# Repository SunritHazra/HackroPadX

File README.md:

# HackroPadX

HackroPadX is my custom 3x3 mechanical macropad built around the Seeed Studio XIAO RP2040. It has 9 programmable mechanical keys in a clean grid, a rotary encoder with push button, and a 0.96 inch OLED screen that shows useful info.

Isn’t the name cool? I "smartly" mixed up "Marcro" and "Hack" to come up with a clever name, as I kind of struggling to find a name. And the "X" is just chilling there.

I made it because I wanted a compact, nice-looking macropad for quick shortcuts, media control, volume adjustment, and custom macros without taking up too much space. It works great for video editing, coding, streaming, or just controlling your music and system functions. Since it’s fully open source, you can change anything to fit your workflow. And also becuause everyone builds a Macro Pad for Blueprint.

### Fusion Render & Snapshot

---

### PCB and Schematic

---

### PCBA Renders & 3D Views

---

### Bill of Materials

Here’s everything needed to build one. I’ve included direct links for convinience:

- **Seeed Studio XIAO RP2040** → [Seeed Studio official store](https://www.seeedstudio.com/Seeed-XIAO-RP2040-p-5026.html) or [Amazon](https://www.amazon.com/Seeed-Studio-XIAO-RP2040/dp/B09V5Y7Z9Q)
- **9× Cherry MX compatible switches** → [KBDfans](https://kbdfans.com/collections/cherry-mx-switches) or [Amazon](https://www.amazon.com/Cherry-MX-Switches-Mechanical-Keyboard/dp/B07Z5K8Z5Z)
- **9× 1N4148 diodes (DO-35)** → [Digi-Key](https://www.digikey.com/en/products/detail/on-semiconductor/1N4148/458603) or [Amazon](https://www.amazon.com/1N4148-Diode-100pcs/dp/B07Z5K8Z5Z)
- **0.96" I2C OLED module (128x64 SSD1306)** → [Amazon](https://www.amazon.com/0-96-inch-OLED-Display-Module/dp/B07Z5K8Z5Z)
- **Rotary encoder (Alps EC11 with push switch)** → [Amazon](https://www.amazon.com/EC11-Rotary-Encoder-Switch/dp/B07Z5K8Z5Z) or [AliExpress](https://www.aliexpress.com/item/1005001234567890.html)
- **9× 1u keycaps** → [KBDfans](https://kbdfans.com/collections/keycaps) or any standard 1u set
- **HackroPadX PCB** → Order from JLCPCB using the Gerbers in this repo

Note that the BOM has components listed as "Kit" as I am expecting to receive a kit with those parts from Blueprint.

---

### Assembly Instructions

Assembling the board is pretty straightforward. There are no screws, no fasteners, no magnets, only pure faith on gravity and friction. So, don't you use your HackPadX in space or in a hypothetical scenario where there is no friction. There are 4 circular extrusions projecting out down from the Case Top, and they line up with the holes in the PCB and the Case Bottom. I hope the images can help you better understand.

I guess the friction is enough to not cause any assembly disturbances. But why did I do like that? Because I didn't want to get into the mess of using screws for such a small project, and I am pretty sure this would be stationary. And I can absolutely not use glue.

---

### Soldering

Building it is pretty straightforward. I recommend soldering in this order:

- Solder the 9 diodes first — make sure the black band matches the marking on the PCB.
- Solder the rotary encoder on the right side.
- Solder the OLED module, carefully aligning the pins (VCC, GND, SCL, SDA).
- Solder the XIAO RP2040 — do both the castellated edges and through-holes for a solid connection.
- Finally, insert and solder the 9 mechanical switches. Push them all the way down so they sit flat.

After soldering, clean the board. If you’re using a 3D printed case, mount the PCB with standoffs, add rubber feet underneath, snap on the keycaps, and push the knob onto the encoder.

**Note:** All components (including the OLED and encoder) solder directly to the PCB — there are no loose wires, so no separate wiring diagram is needed. Everything is shown clearly in the schematic and 3D renders above. And of course every component is properly named on the PCB.

---

### Firmware Flashing Instructions

HackroPadX runs on CircuitPython with the KMK framework. Here’s how to flash it:

**Step 1: Install CircuitPython**  
- Download the latest CircuitPython UF2 for Seeed XIAO RP2040 from circuitpython.org.  
- Hold the BOOT button while plugging in USB-C. The board will show up as **RPI-RP2**.  
- Copy the UF2 file to that drive. It will restart and appear as **CIRCUITPY**.

**Step 2: Add KMK and OLED Library**  
- Download KMK from github.com/KMKfw/kmk_firmware and copy the entire `kmk` folder to the CIRCUITPY drive.  
- Add the `adafruit_displayio_ssd1306` library for the OLED.

**Step 3: Upload the Code**  
- Copy the `HackroPadX Firmware.py` file (included in this repo) to the root of the CIRCUITPY drive and rename it to `code.py`.  
- Safely eject the drive.

Once plugged in, it should work as a keyboard and the OLED will light up.

---

### How to Use It

By default the keys do these functions:

- **Top row**: Volume Up – Mute – Volume Down  
- **Middle row**: Previous Track – Play/Pause – Next Track  
- **Bottom row**: Copy – Paste – Cut  

**Rotary Encoder:**  
- Turn left → Volume Down  
- Turn right → Volume Up  
- Press → Mute  

The 0.96" OLED screen shows “HackroPadX” and the current layer.

You can customize everything easily — just edit the `HackroPadX Firmware.py` file (rename it to `code.py` first) on the CIRCUITPY drive to change key functions, add layers, modify the encoder, or update the OLED text.

---

**Files included in this repo**  
- Full KiCad project (.kicad_pro, .kicad_sch, .kicad_pcb) + Gerbers  
- Fusion 360 CAD model (.f3d) + STEP export  
- Complete BOM with purchase links  
- Full firmware (`HackroPadX Firmware.py`)  
- All the renders and photos you see above  

---

And that's all. I hope this README.md will help at least someone build a macro pad.

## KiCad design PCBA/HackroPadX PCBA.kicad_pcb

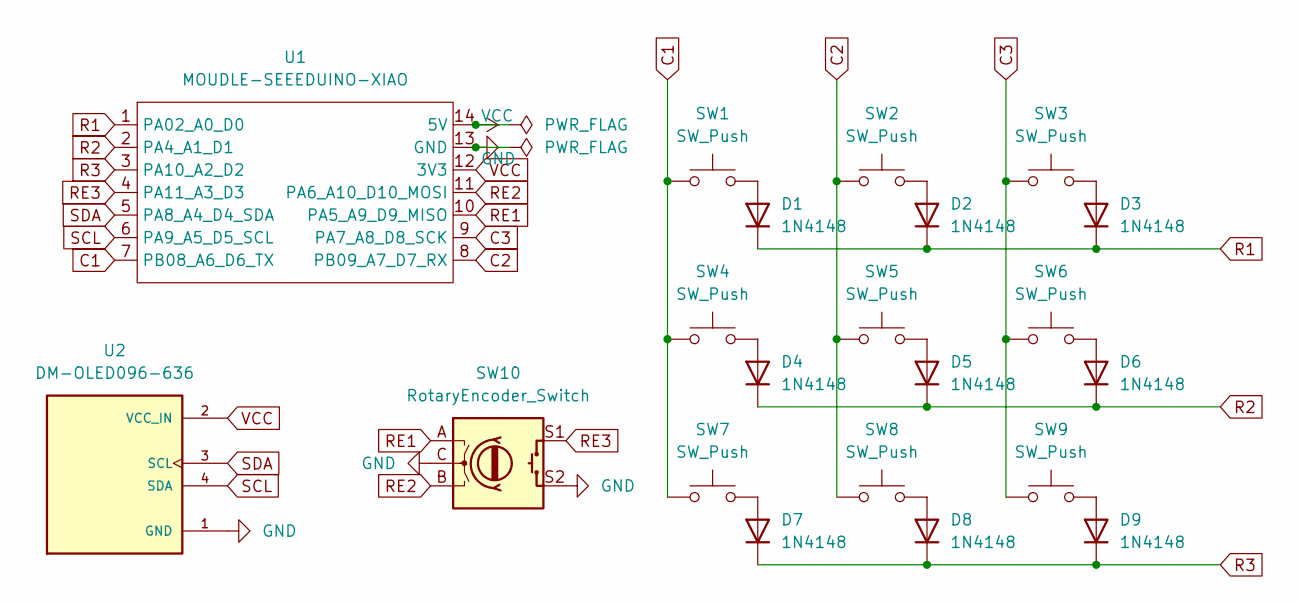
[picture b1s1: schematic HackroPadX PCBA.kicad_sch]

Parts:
D1, D2, D3, D4, D5, D6, D7, D8, D9: 1N4148; D_DO-35_SOD27_P7.62mm_Horizontal
SW1, SW2, SW3, SW4, SW5, SW6, SW7, SW8, SW9: SW_Push; SW_Cherry_MX_1.00u_PCB
SW10: RotaryEncoder_Switch; RotaryEncoder_Alps_EC11E-Switch_Vertical_H20mm
U1: MOUDLE-SEEEDUINO-XIAO; XIAO-Generic-Hybrid-14P-2.54-21X17.8MM
U2: DM-OLED096-636; MODULE_DM-OLED096-636; PARTREV 2018-09-10

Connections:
C1: SW1.1, SW4.1, SW7.1, U1.7 (PB08_A6_D6_TX)
C2: SW2.1, SW5.1, SW8.1, U1.8 (PB09_A7_D7_RX)
C3: SW3.1, SW6.1, SW9.1, U1.9 (PA7_A8_D8_SCK)
GND: SW10.C, SW10.S2, U1.13 (GND), U2.1 (GND)
unnamed: D1.2 (A), SW1.2
unnamed: D2.2 (A), SW2.2
unnamed: D3.2 (A), SW3.2
unnamed: D4.2 (A), SW4.2
unnamed: D5.2 (A), SW5.2
unnamed: D6.2 (A), SW6.2
unnamed: D7.2 (A), SW7.2
unnamed: D8.2 (A), SW8.2
unnamed: D9.2 (A), SW9.2
R1: D1.1 (K), D2.1 (K), D3.1 (K), U1.1 (PA02_A0_D0)
R2: D4.1 (K), D5.1 (K), D6.1 (K), U1.2 (PA4_A1_D1)
R3: D7.1 (K), D8.1 (K), D9.1 (K), U1.3 (PA10_A2_D2)
RE1: SW10.A, U1.10 (PA5_A9_D9_MISO)
RE2: SW10.B, U1.11 (PA6_A10_D10_MOSI)
RE3: SW10.S1, U1.4 (PA11_A3_D3)
SCL: U1.6 (PA9_A5_D5_SCL), U2.4 (SDA)
SDA: U1.5 (PA8_A4_D4_SDA), U2.3 (SCL)
VCC: U1.12 (3V3), U1.14 (5V), U2.2 (VCC_IN)

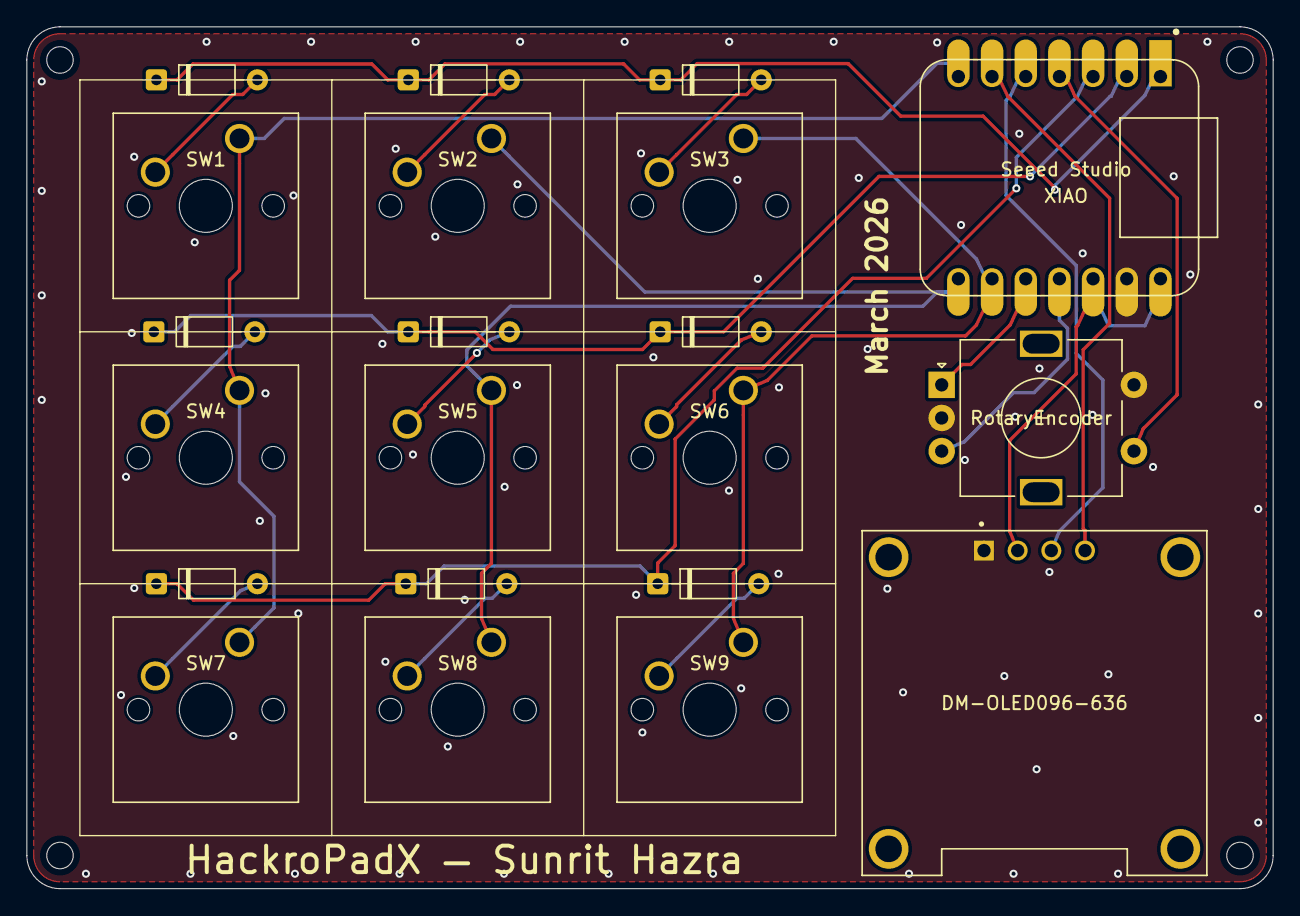
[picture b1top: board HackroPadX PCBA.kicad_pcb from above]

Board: 2 copper layers, 94.0 x 65.0 mm, 21 parts (0 on the bottom side), 22 nets.

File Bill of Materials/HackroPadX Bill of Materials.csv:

Category,Name,Quantity,Price,Links
PCBA,PCB,1,2.00,https://jlcpcb.com/
PCBA,1N4148 Diodes,9,,Kit
PCBA,Cherry Max Switches,9,,Kit
PCBA,Rotary Encoder,1,,Kit
PCBA,MOUDLE-SEEEDUINO-XIAO,1,,Kit
PCBA,DM-OLED096-636,1,3.19,https://amzn.in/d/01MaqbYK
Case,Case Bottom,1,3.37,https://jlc3dp.com/?spm=Jlc3dp.Homepage.1001
Case,Case Top,1,1.61,https://jlc3dp.com/?spm=Jlc3dp.Homepage.1002
Keycaps,Keycaps,9,,Kit
Knob,Knob,1,0.31,https://jlc3dp.com/?spm=Jlc3dp.Homepage.1004
Shipping,JLC3DP E-POST Shipping,,11.01,
Shipping,JLCPCB E-POST Shipping,,10.07,
Total,Total,,31.56,

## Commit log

2026-03-24 Rename HacroPadX PCBA 3D Model.jpg to HackroPadX PCBA 3D Model.jpg
